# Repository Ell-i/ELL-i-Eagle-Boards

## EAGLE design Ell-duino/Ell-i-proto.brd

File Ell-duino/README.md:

Ell-duino -- the first ELL-i prototype board
============================================

This directory contains the Ell-duino Ell-i board design, mainly for
historical reasons.

Ell-duino was the very first PCB produced by the Ell-i co-operative,
with 50 pieces manufactured in late May 2013.  It was an
STM32F051-based board, header-compatible with Arduino.  It taught us a
lot, guiding us with designing the next round of boards, and acting as
a testing platform even after that.

Used libraries
--------------

Contrary to the other projects in this repository, this design used a
local Eagle library, ell-i.lbr.  By now that library is obsolete and
should not be used any more.  Instead, you are adviced to use the
components from the SparkFun or ELL-i Eagle libraries.

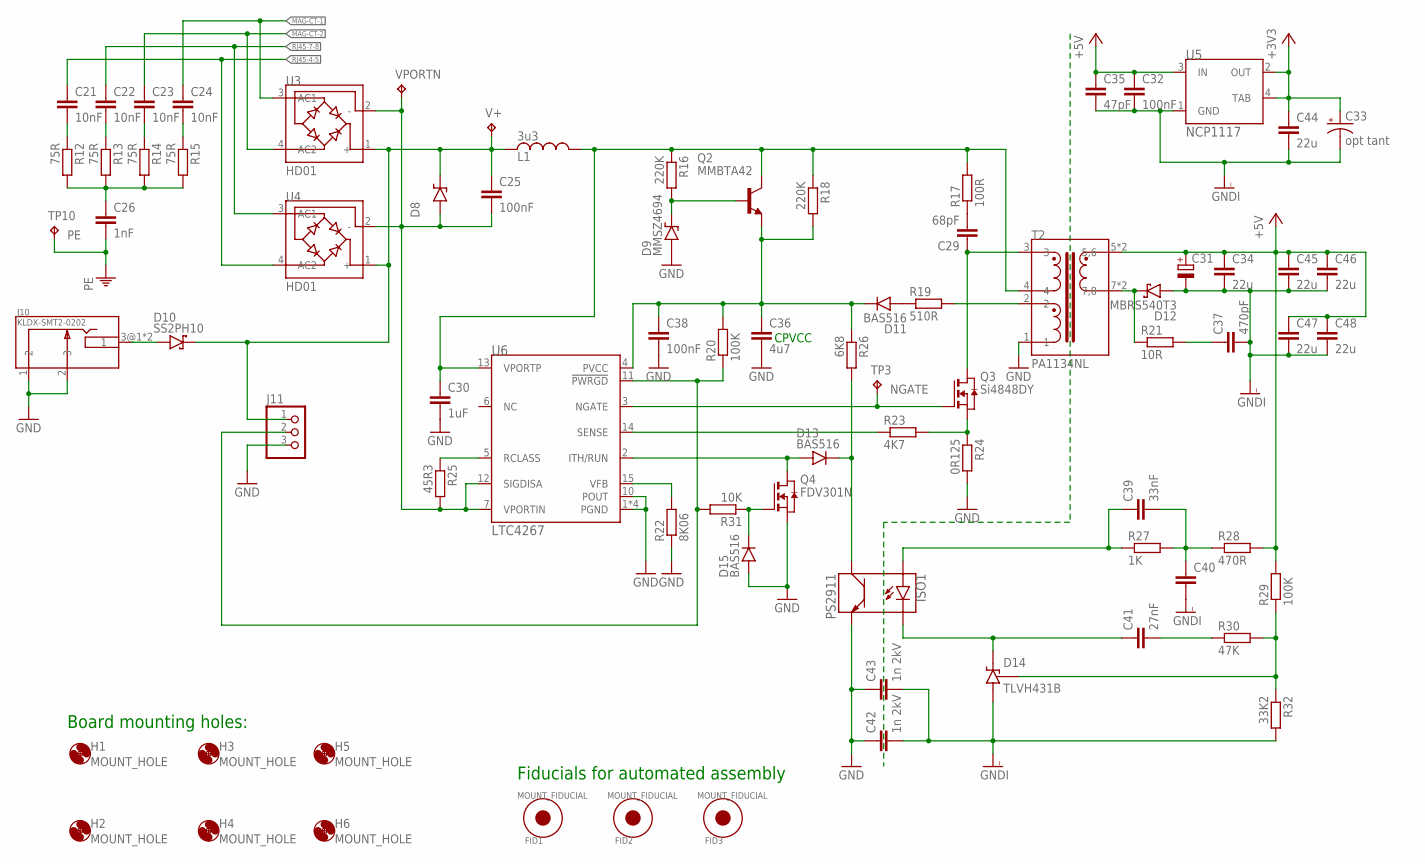
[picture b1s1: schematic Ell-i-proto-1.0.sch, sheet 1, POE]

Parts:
C21, C22, C23, C24: 10nF; 0603
C25: 100nF; 0805
C26: 1nF; C1206
C29: 68pF; 0805
C30: 1uF; 0805
C31: CPOL-EU153CLV-0605; 153CLV-0605
C32, C38: 100nF; 0402
C33: opt tant; CT3216
C34, C44, C45, C46, C47, C48: 22u; 0805
C35: 47pF; 0402
C36: 4u7; 0805
C37: 470pF; 0402
C39: 33nF; 0402
C40: C0402; 0402
C41: 27nF; 0402
C42, C43: 1n 2kV; C1206
D8: SMAJ58A; SMA
D9: MMSZ4694; SOD-123
D10: SS2PH10; SMP
D11, D13, D15: BAS516; SOD523
D12: MBRS540T3; SMC
D14: TLVH431B; SOT23
FID1, FID2, FID3: MOUNT_FIDUCIAL
H1, H2, H3, H4, H5, H6: MOUNT_HOLE
ISO1: PS2911
J10: KLDX-SMT2-0202
J11: PINHD-1X3; 1X03
L1: 3u3; MSS5121
Q2: MMBTA42; SOT23
Q3: Si4848DY; SO8
Q4: FDV301N; SOT23
R12, R13, R14, R15: 75R; 0603
R16, R18: 220K; 0402
R17: 100R; 0805
R19: 510R; 0402
R20, R29: 100K; 0402
R21: 10R; 0402
R22: 8K06; 0402
R23: 4K7; 0402
R24: 0R125; R1206
R25: 45R3; 0402
R26: 6K8; 0402
R27: 1K; 0402
R28: 470R; 0402
R30: 47K; 0402
R31: 10K; 0402
R32: 33K2; 0402
T2: PA1134NL
TP3, TP10: TPB1,27; B1,27
U3, U4: HD01; MINIDIP4
U5: NCP1117; SOT223
U6: LTC4267; SSOP16
V+: TPB1,27; B1,27
VPORTN: TPB1,27; B1,27

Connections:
+3V3: C33.+, C44.1, U5.2 (OUT), U5.4 (TAB); also elsewhere on the board
+5V: C31.+, C32.1, C34.1, C35.1, C45.1, C46.1, C47.1, C48.1, R28.2, R29.2, T2.5 (5,6), T2.6 (5,6), U5.3 (IN); also elsewhere on the board
GND: C30.2, C36.2, C38.2, C42.1, C43.1, D9.A, D15.2 (A), ISO1.3, J10.1 (2), J10.2 (3), J11.3, Q4.2 (S), R22.1, R24.2, T2.1, U6.1 (PGND), U6.8 (PGND), U6.9 (PGND), U6.10 (POUT), U6.16 (PGND)
GNDI: C31.-, C32.2, C33.-, C34.2, C35.2, C37.2, C40.2, C42.2, C43.2, C44.2, C45.2, C46.2, C47.2, C48.2, D12.2 (A), D14.3 (A), R32.2, U5.1 (GND); also elsewhere on the board
MAG-CT-1: C24.1, U3.3 (AC1); also elsewhere on the board
MAG-CT-2: C23.1, U3.4 (AC2); also elsewhere on the board
N22741: C21.2, R12.1
N22792: C22.2, R13.1
N22914: C26.1, R12.2, R13.2, R14.2, R15.2
N23144: C23.2, R14.1
N23171: C24.2, R15.1
N27571: C29.1, Q3.P$5 (D), Q3.P$6 (D), Q3.P$7 (D), Q3.P$8 (D), T2.3
N27735: Q3.P$1 (S), Q3.P$2 (S), Q3.P$3 (S), R23.2, R24.1
N28455: R23.1, U6.14 (SENSE)
N30165: C36.1, C38.1, D11.1 (C), Q2.2 (E), R18.2, R20.2, R26.1, U6.4 (PVCC)
N30229: D11.2 (A), R19.1
N30416: D13.2 (A), Q4.3 (D), U6.2 (ITH/RUN)
N32035: D15.1 (C), Q4.1 (G), R31.1
N36998: R22.2, U6.15 (VFB)
N40108: D14.1 (REF), R29.1, R30.2, R32.1
N40137: C41.1, D14.2 (C), ISO1.2
N40177: C39.1, ISO1.1, R27.1
N40361: D12.1 (C), R21.1, T2.7 (7,8), T2.8 (7,8)
N40778: C37.1, R21.2
N62909: C30.1, L1.2, Q2.3 (C), R16.1, R17.2, R18.1, T2.4, U6.13 (VPORTP)
N62998: D9.C, Q2.1 (B), R16.2
N64947: R25.1, U6.5 (RCLASS)
N68062: R19.2, T2.2
N68837: C29.2, R17.1
N69576: D13.1 (C), ISO1.4, R26.2
N69902: C41.2, R30.1
N70322: C39.2, C40.1, R27.2, R28.1
N184903: D10.A, J10.3@1 (1), J10.3@2 (1)
NGATE: Q3.P$4 (G), TP3.TP, U6.3 (NGATE)
NPWRGD: J11.2, R20.1, R31.2, U6.11 (!PWRGD)
PE: C26.2, TP10.TP; also elsewhere on the board
RJ45-4-5: C21.1, U4.4 (AC2); also elsewhere on the board
RJ45-7-8: C22.1, U4.3 (AC1); also elsewhere on the board
V+: C25.1, D8.1 (C), D10.C, J11.1, L1.1, U3.1 (+), U4.1 (+), V+.TP
VPORTN: C25.2, D8.2 (A), R25.2, U3.2 (-), U4.2 (-), U6.7 (VPORTIN), U6.12 (SIGDISA), VPORTN.TP

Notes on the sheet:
CPVCC
Board mounting holes:
Fiducials for automated assembly

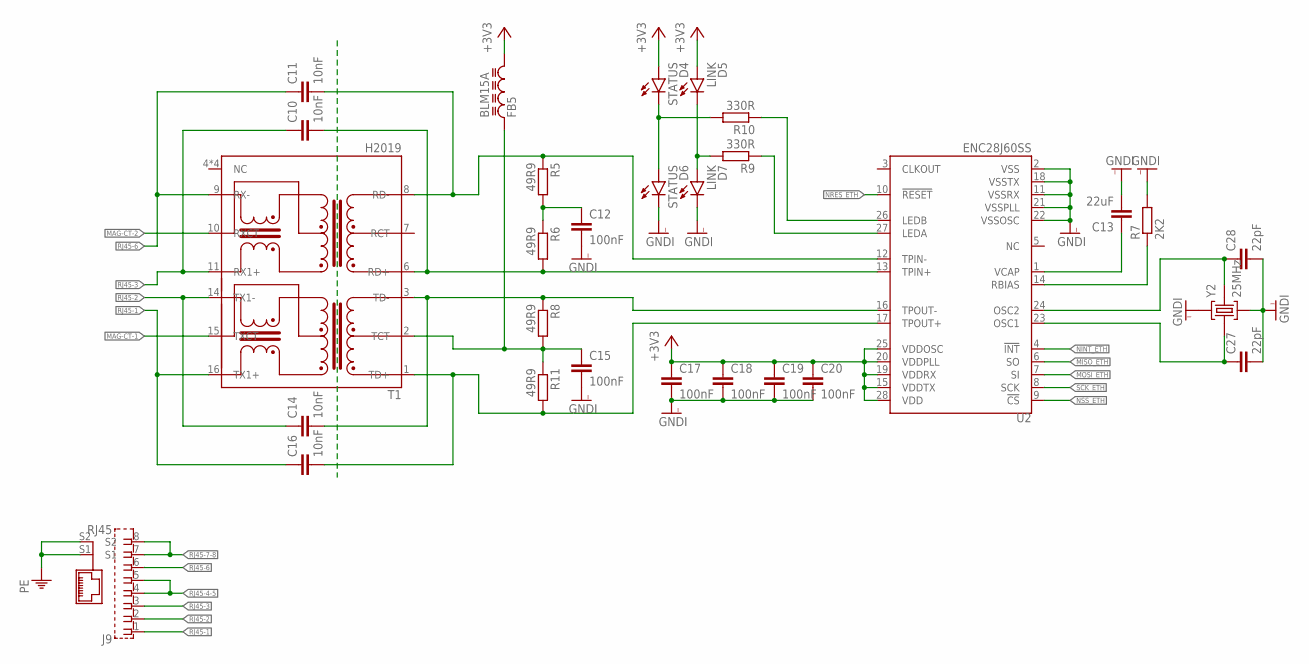
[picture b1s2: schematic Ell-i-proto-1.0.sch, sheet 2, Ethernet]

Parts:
C10, C11, C14, C16: 10nF; C1206
C12, C15, C17, C18, C19, C20: 100nF; 0402
C13: 22uF; 0805
C27, C28: 22pF; 0402
D4, D6: STATUS; DIODE0603
D5, D7: LINK; DIODE0603
FB5: BLM15A; 0402
J9: RJ45; 85502-5008
R5, R6, R8, R11: 49R9; 0402
R7: 2K2; 0402
R9, R10: 330R; 0402
T1: H2019; H2019NL
U2: ENC28J60SS; SSOP28DB
Y2: 25MHz; XTAL3225

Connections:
+3V3: C17.1, C18.1, C19.1, C20.1, D4.2 (A), D5.2 (A), FB5.2, U2.15 (VDDTX), U2.19 (VDDRX), U2.20 (VDDPLL), U2.25 (VDDOSC), U2.28 (VDD); also elsewhere on the board
GNDI: C12.2, C13.2, C15.2, C17.2, C18.2, C19.2, C20.2, C27.2, C28.2, D6.1 (C), D7.1 (C), R7.2, U2.2 (VSS), U2.11 (VSSRX), U2.18 (VSSTX), U2.21 (VSSPLL), U2.22 (VSSOSC), Y2.2 (GND), Y2.4 (GND); also elsewhere on the board
MAG-CT-1: T1.15 (TXCT); also elsewhere on the board
MAG-CT-2: T1.10 (RXCT); also elsewhere on the board
MISO_ETH: U2.6 (SO); also elsewhere on the board
MOSI_ETH: U2.7 (SI); also elsewhere on the board
N08557: C14.2, R8.1, T1.3 (TD-), U2.16 (TPOUT-)
N08738: C16.2, R11.2, T1.1 (TD+), U2.17 (TPOUT+)
N08782: C10.2, R6.2, T1.6 (RD+), U2.13 (TPIN+)
N08928: C11.2, R5.1, T1.8 (RD-), U2.12 (TPIN-)
N12266: C15.1, FB5.1, R8.2, R11.1, T1.2 (TCT)
N12583: R7.1, U2.14 (RBIAS)
N13468: C28.1, U2.24 (OSC2), Y2.3 (C2)
N13660: C27.1, U2.23 (OSC1), Y2.1 (C1)
N14101: C13.1, U2.1 (VCAP)
N16078: C12.1, R5.2, R6.1
N181699: R9.1, U2.27 (LEDA)
N181770: R10.1, U2.26 (LEDB)
N182309: D4.1 (C), D6.2 (A), R10.2
unnamed: D5.1 (C), D7.2 (A), R9.2
NINT_ETH: U2.4 (!INT); also elsewhere on the board
NRES_ETH: U2.10 (!RESET); also elsewhere on the board
NSS_ETH: U2.9 (!CS); also elsewhere on the board
PE: J9.S1, J9.S2; also elsewhere on the board
RJ45-1: C16.1, J9.1, T1.16 (TX1+)
RJ45-2: C14.1, J9.2, T1.14 (TX1-)
RJ45-3: C10.1, J9.3, T1.11 (RX1+)
RJ45-4-5: J9.4, J9.5; also elsewhere on the board
RJ45-6: C11.1, J9.6, T1.9 (RX-)
RJ45-7-8: J9.7, J9.8; also elsewhere on the board
SCK_ETH: U2.8 (SCK); also elsewhere on the board

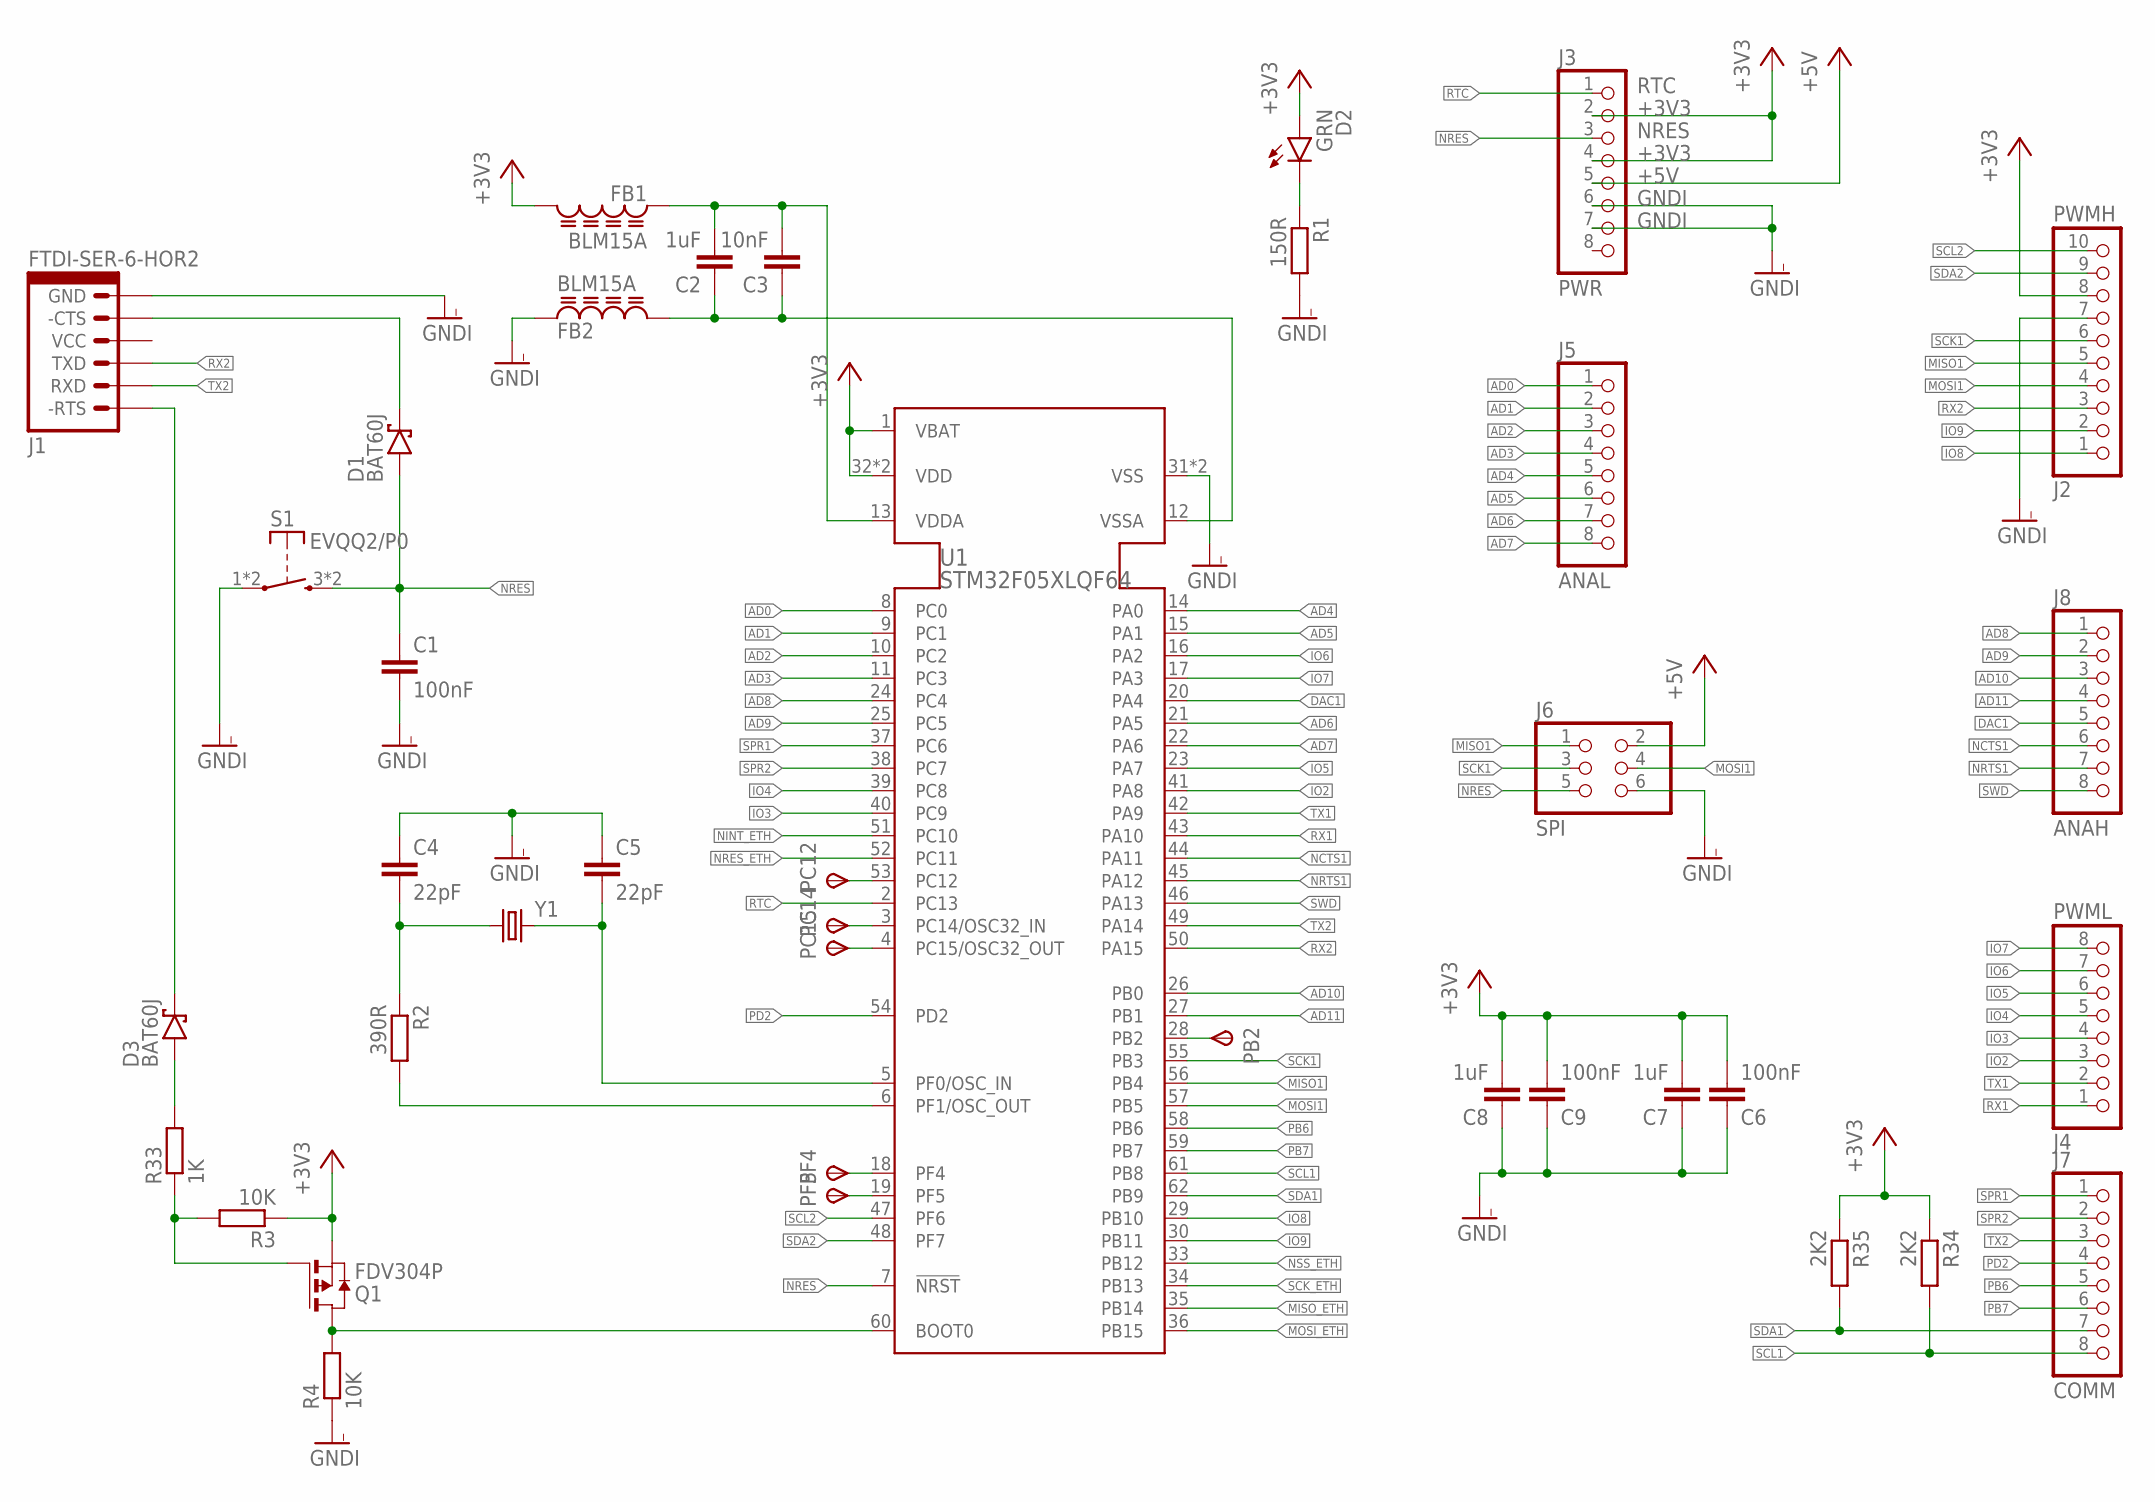
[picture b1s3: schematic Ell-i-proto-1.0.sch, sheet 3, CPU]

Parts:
C1, C6, C9: 100nF; 0402
C2, C7, C8: 1uF; 0402
C3: 10nF; 0402
C4, C5: 22pF; 0402
D1, D3: BAT60J; SOD323_DIODE
D2: GRN; DIODE0603
FB1, FB2: BLM15A; 0402
J1: FTDI-SER-6-HOR2; TSM-106-01-L-SH-REV
J2: PWMH; 1X10
J3: PWR; 1X08
J4: PWML; 1X08
J5: ANAL; 1X08
J6: SPI; 2X03
J7: COMM; 1X08
J8: ANAH; 1X08
PB2: TPSB1,27; B1,27
PC12, PC14, PC15: TPSB1,27; B1,27
PF4, PF5: TPSB1,27; B1,27
Q1: FDV304P; SOT23
R1: 150R; 0402
R2: 390R; 0402
R3, R4: 10K; 0402
R33: 1K; 0402
R34, R35: 2K2; 0402
S1: EVQQ2/P0
U1: STM32F05XLQF64; LQFP64
Y1: CRYSTALSM49; SM49

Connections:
+3V3: C6.2, C7.2, C8.2, C9.2, D2.2 (A), FB1.2, J2.8, J3.2, J3.4, Q1.2 (S), R3.1, R34.1, R35.1, U1.1 (VBAT), U1.32 (VDD), U1.64 (VDD); also elsewhere on the board
+5V: J3.5, J6.2; also elsewhere on the board
AD0: J5.1, U1.8 (PC0)
AD1: J5.2, U1.9 (PC1)
AD2: J5.3, U1.10 (PC2)
AD3: J5.4, U1.11 (PC3)
AD4: J5.5, U1.14 (PA0)
AD5: J5.6, U1.15 (PA1)
AD6: J5.7, U1.21 (PA5)
AD7: J5.8, U1.22 (PA6)
AD8: J8.1, U1.24 (PC4)
AD9: J8.2, U1.25 (PC5)
AD10: J8.3, U1.26 (PB0)
AD11: J8.4, U1.27 (PB1)
DAC1: J8.5, U1.20 (PA4)
GNDI: C1.2, C4.1, C5.1, C6.1, C7.1, C8.1, C9.1, FB2.1, J1.1 (GND), J2.7, J3.6, J3.7, J6.6, R1.2, R4.1, S1.1, S1.2, U1.31 (VSS), U1.63 (VSS); also elsewhere on the board
IO2: J4.3, U1.41 (PA8)
IO3: J4.4, U1.40 (PC9)
IO4: J4.5, U1.39 (PC8)
IO5: J4.6, U1.23 (PA7)
IO6: J4.7, U1.16 (PA2)
IO7: J4.8, U1.17 (PA3)
IO8: J2.1, U1.29 (PB10)
IO9: J2.2, U1.30 (PB11)
MISO1: J2.5, J6.1, U1.56 (PB4)
MISO_ETH: U1.35 (PB14); also elsewhere on the board
MOSI1: J2.4, J6.4, U1.57 (PB5)
MOSI_ETH: U1.36 (PB15); also elsewhere on the board
N41567: D2.1 (C), R1.1
N98218: C2.1, C3.1, FB2.2, U1.12 (VSSA)
N100630: C2.2, C3.2, FB1.1, U1.13 (VDDA)
N118561: Q1.3 (D), R4.2, U1.60 (BOOT0)
N205481: C4.2, R2.1, Y1.1
N209164: Q1.1 (G), R3.2, R33.1
N230488: D3.2 (A), R33.2
unnamed: PC14.TP, U1.3 (PC14/OSC32_IN)
unnamed: PC15.TP, U1.4 (PC15/OSC32_OUT)
unnamed: PF4.TP, U1.18 (PF4)
unnamed: D1.1 (C), J1.2 (-CTS)
unnamed: PF5.TP, U1.19 (PF5)
unnamed: PB2.TP, U1.28 (PB2)
unnamed: PC12.TP, U1.53 (PC12)
NCTS1: J8.6, U1.44 (PA11)
NDSR2: D3.1 (C), J1.6 (-RTS)
NINT_ETH: U1.51 (PC10); also elsewhere on the board
NRES: C1.1, D1.2 (A), J3.3, J6.5, S1.3 (S), S1.4 (S), U1.7 (!NRST)
NRES_ETH: U1.52 (PC11); also elsewhere on the board
NRTS1: J8.7, U1.45 (PA12)
NSS_ETH: U1.33 (PB12); also elsewhere on the board
PB6: J7.5, U1.58 (PB6)
PB7: J7.6, U1.59 (PB7)
PD2: J7.4, U1.54 (PD2)
PF0: C5.2, U1.5 (PF0/OSC_IN), Y1.2
PF1: R2.2, U1.6 (PF1/OSC_OUT)
RTC: J3.1, U1.2 (PC13)
RX1: J4.1, U1.43 (PA10)
RX2: J1.4 (TXD), J2.3, U1.50 (PA15)
SCK1: J2.6, J6.3, U1.55 (PB3)
SCK_ETH: U1.34 (PB13); also elsewhere on the board
SCL1: J7.8, R34.2, U1.61 (PB8)
SCL2: J2.10, U1.47 (PF6)
SDA1: J7.7, R35.2, U1.62 (PB9)
SDA2: J2.9, U1.48 (PF7)
SPR1: J7.1, U1.37 (PC6)
SPR2: J7.2, U1.38 (PC7)
SWD: J8.8, U1.46 (PA13)
TX1: J4.2, U1.42 (PA9)
TX2: J1.5 (RXD), J7.3, U1.49 (PA14)

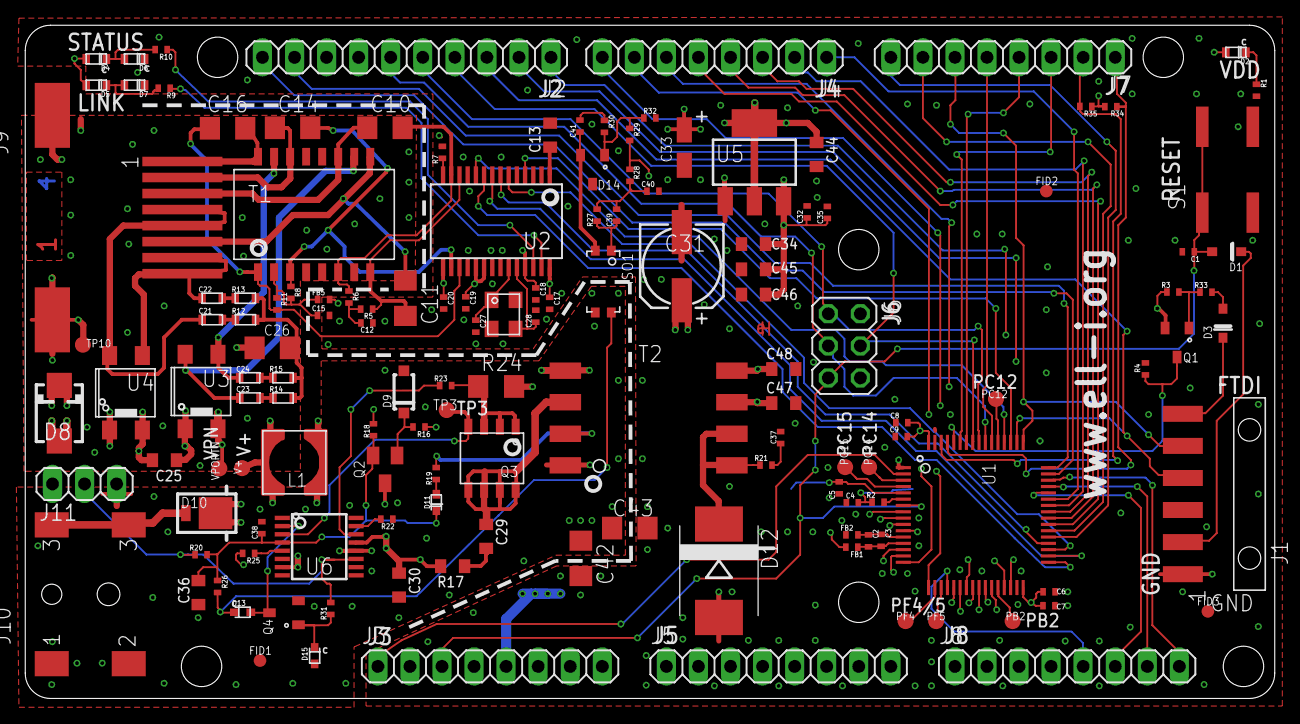
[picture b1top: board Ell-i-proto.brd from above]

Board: 4 copper layers, 99.0 x 53.3 mm, 149 parts (1 on the bottom side), 123 nets.

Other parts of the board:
U$4: EH-LOGO

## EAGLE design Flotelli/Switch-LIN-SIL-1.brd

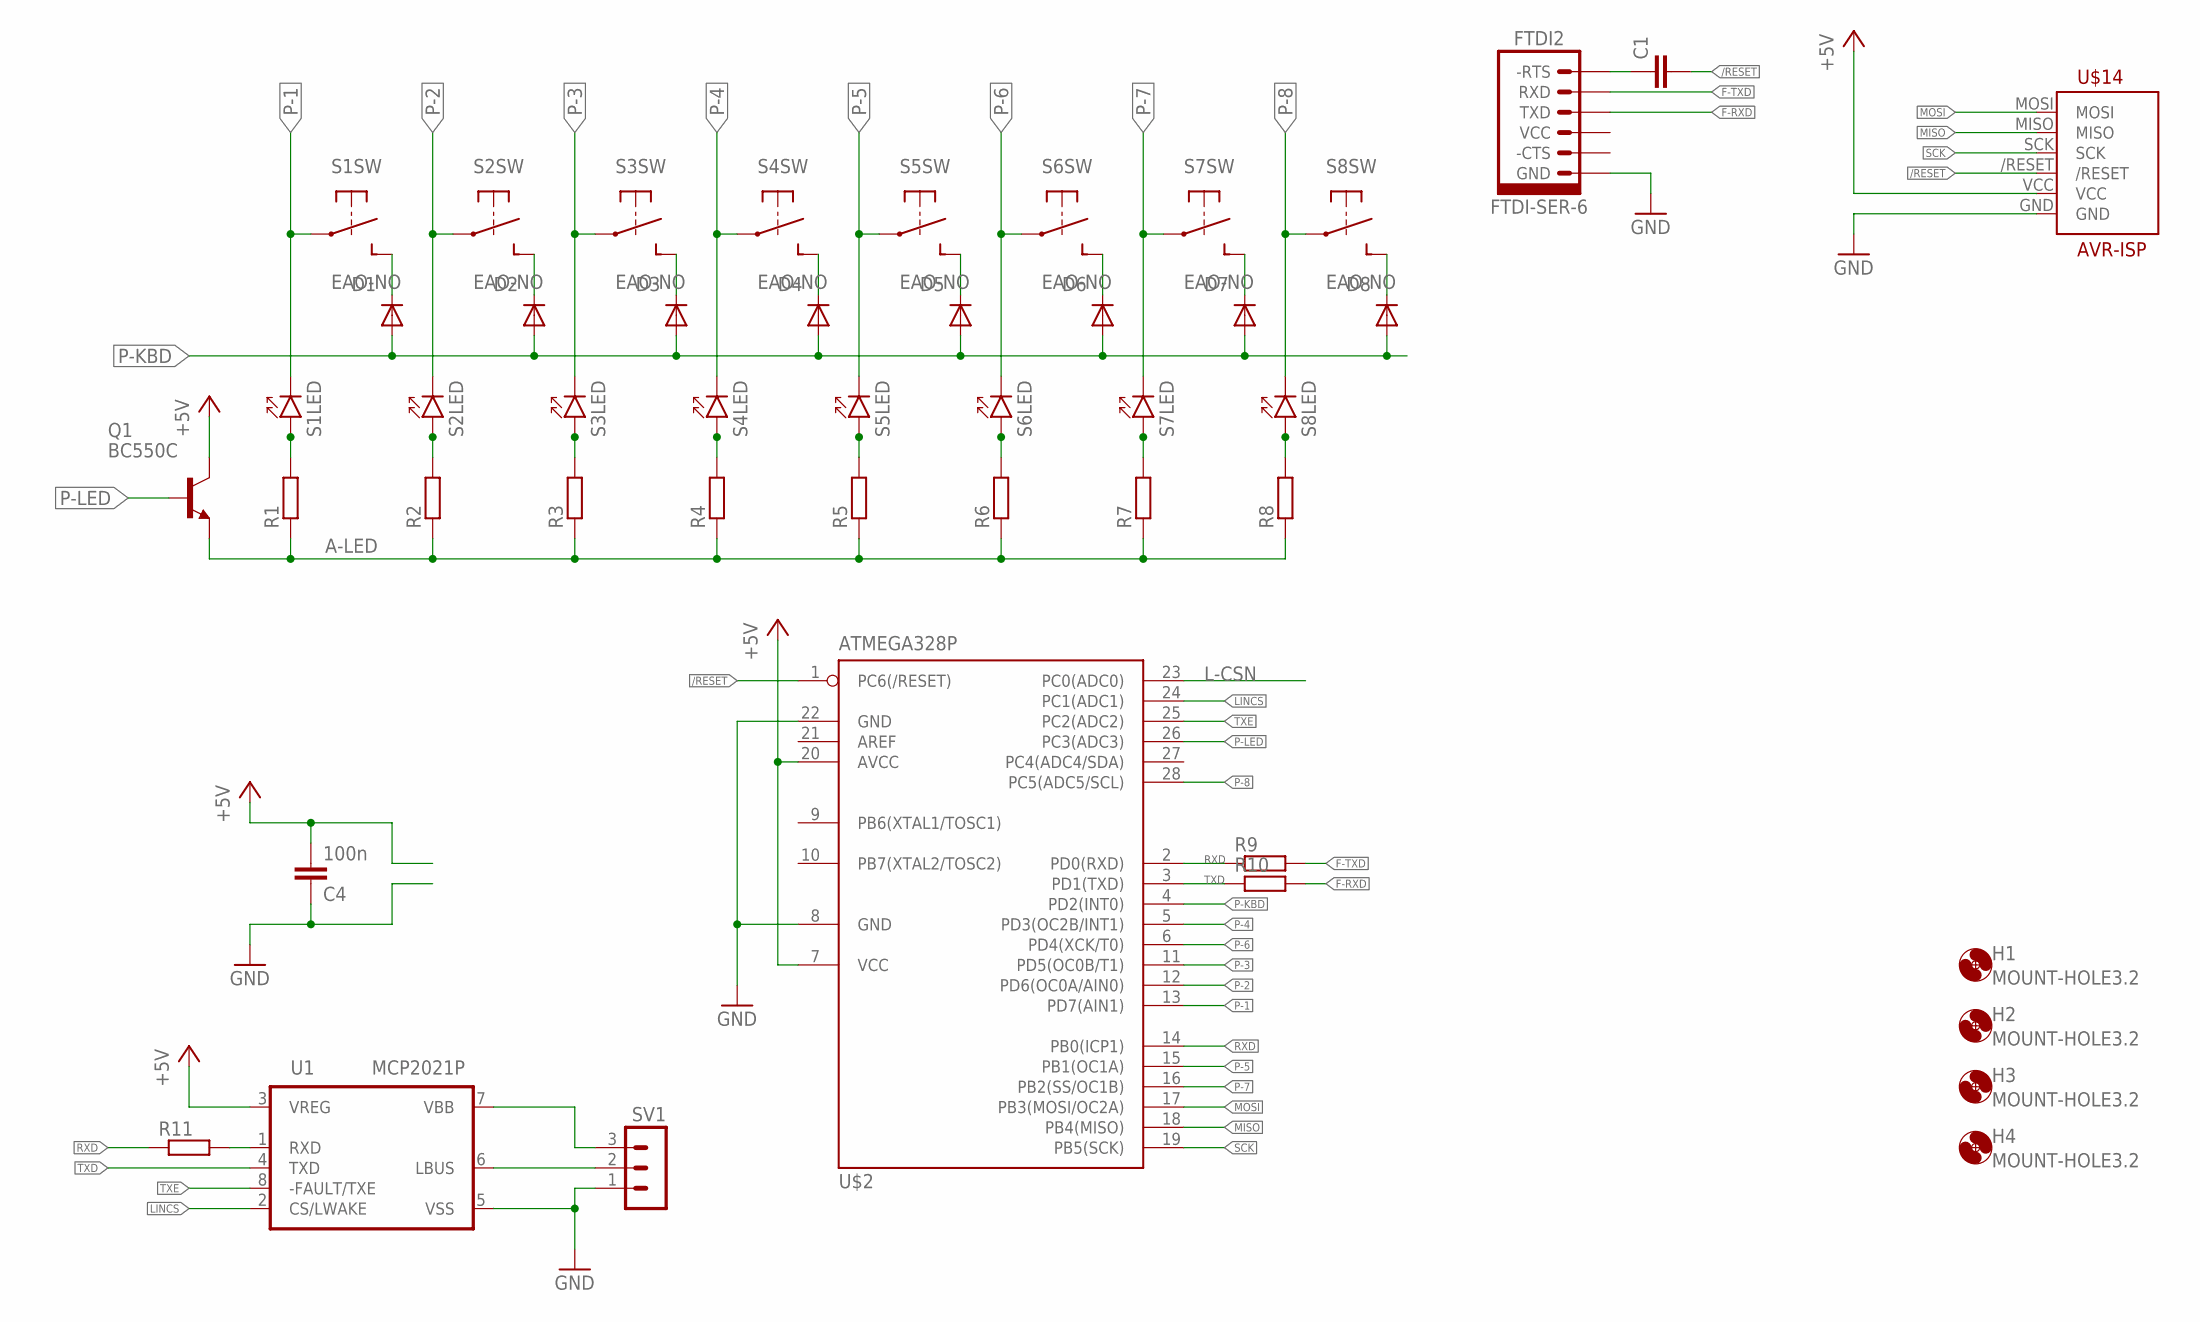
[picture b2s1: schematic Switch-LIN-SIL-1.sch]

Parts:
C1: C-EU025-025X050; C025-025X050
C4: 100n; C0805
D1, D2, D3, D4, D5, D6, D7, D8: 1N4148; DO35-7
FTDI2: FTDI-SER-6
H1, H2, H3, H4: MOUNT-HOLE3.2; 3,2
Q1: BC550C; TO92-EBC
R1, R2, R3, R4, R5, R6, R7, R8, R9, R10, R11: R-EU_0207/7; 0207/7
S1, S2, S3, S4, S5, S6, S7, S8: EAO-NO; MA04-1
SV1: MA03-1
U1: MCP2021P; DIL8
U$2: ATMEGA328P; DIL28-3
U$14: AVR-ISP; AVR-ISP-SIL

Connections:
+5V: C4.2, Q1.C, U1.3 (VREG), U$2.7 (VCC), U$2.20 (AVCC), U$14.VCC
/RESET: C1.2, U$2.1 (PC6(/RESET)), U$14./RESET
A-LED: Q1.E, R1.1, R2.1, R3.1, R4.1, R5.1, R6.1, R7.1, R8.1
F-RTS: C1.1, FTDI2.-RTS
F-RXD: FTDI2.TXD, R10.2
F-TXD: FTDI2.RXD, R9.2
GND: C4.1, FTDI2.GND, SV1.1, U1.5 (VSS), U$2.8 (GND), U$2.22 (GND), U$14.GND
L-CSN: U$2.23 (PC0(ADC0))
L-RXD: R11.2, U1.1 (RXD)
LBUS: SV1.2, U1.6 (LBUS)
LINCS: U1.2 (CS/LWAKE), U$2.24 (PC1(ADC1))
MISO: U$2.18 (PB4(MISO)), U$14.MISO
MOSI: U$2.17 (PB3(MOSI/OC2A)), U$14.MOSI
unnamed: D1.C, S1.4 (NO2)
unnamed: D2.C, S2.4 (NO2)
unnamed: D3.C, S3.4 (NO2)
unnamed: D4.C, S4.4 (NO2)
unnamed: D5.C, S5.4 (NO2)
unnamed: D6.C, S6.4 (NO2)
unnamed: D7.C, S7.4 (NO2)
unnamed: D8.C, S8.4 (NO2)
unnamed: R1.2, S1.2 (A)
unnamed: R2.2, S2.2 (A)
unnamed: R3.2, S3.2 (A)
unnamed: R4.2, S4.2 (A)
unnamed: R5.2, S5.2 (A)
unnamed: R6.2, S6.2 (A)
unnamed: R7.2, S7.2 (A)
unnamed: R8.2, S8.2 (A)
P-1: S1.1 (C), S1.3 (NO1), U$2.13 (PD7(AIN1))
P-2: S2.1 (C), S2.3 (NO1), U$2.12 (PD6(OC0A/AIN0))
P-3: S3.1 (C), S3.3 (NO1), U$2.11 (PD5(OC0B/T1))
P-4: S4.1 (C), S4.3 (NO1), U$2.5 (PD3(OC2B/INT1))
P-5: S5.1 (C), S5.3 (NO1), U$2.15 (PB1(OC1A))
P-6: S6.1 (C), S6.3 (NO1), U$2.6 (PD4(XCK/T0))
P-7: S7.1 (C), S7.3 (NO1), U$2.16 (PB2(SS/OC1B))
P-8: S8.1 (C), S8.3 (NO1), U$2.28 (PC5(ADC5/SCL))
P-KBD: D1.A, D2.A, D3.A, D4.A, D5.A, D6.A, D7.A, D8.A, U$2.4 (PD2(INT0))
P-LED: Q1.B, U$2.26 (PC3(ADC3))
RXD: R9.1, R11.1, U$2.2 (PD0(RXD)), U$2.14 (PB0(ICP1))
SCK: U$2.19 (PB5(SCK)), U$14.SCK
TXD: R10.1, U1.4 (TXD), U$2.3 (PD1(TXD))
TXE: U1.8 (-FAULT/TXE), U$2.25 (PC2(ADC2))
VBB: SV1.3, U1.7 (VBB)

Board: 2 copper layers, 39 parts (1 on the bottom side), 43 nets, no tracks yet.

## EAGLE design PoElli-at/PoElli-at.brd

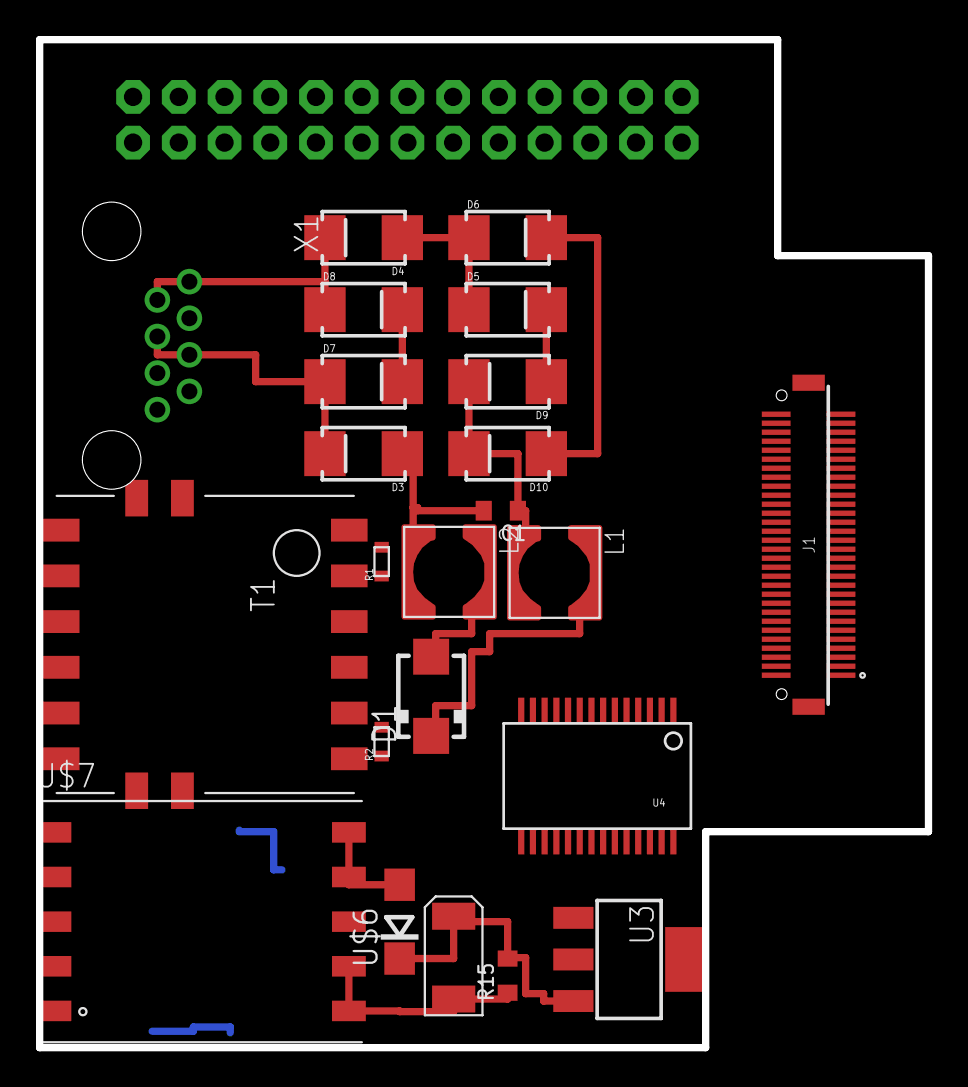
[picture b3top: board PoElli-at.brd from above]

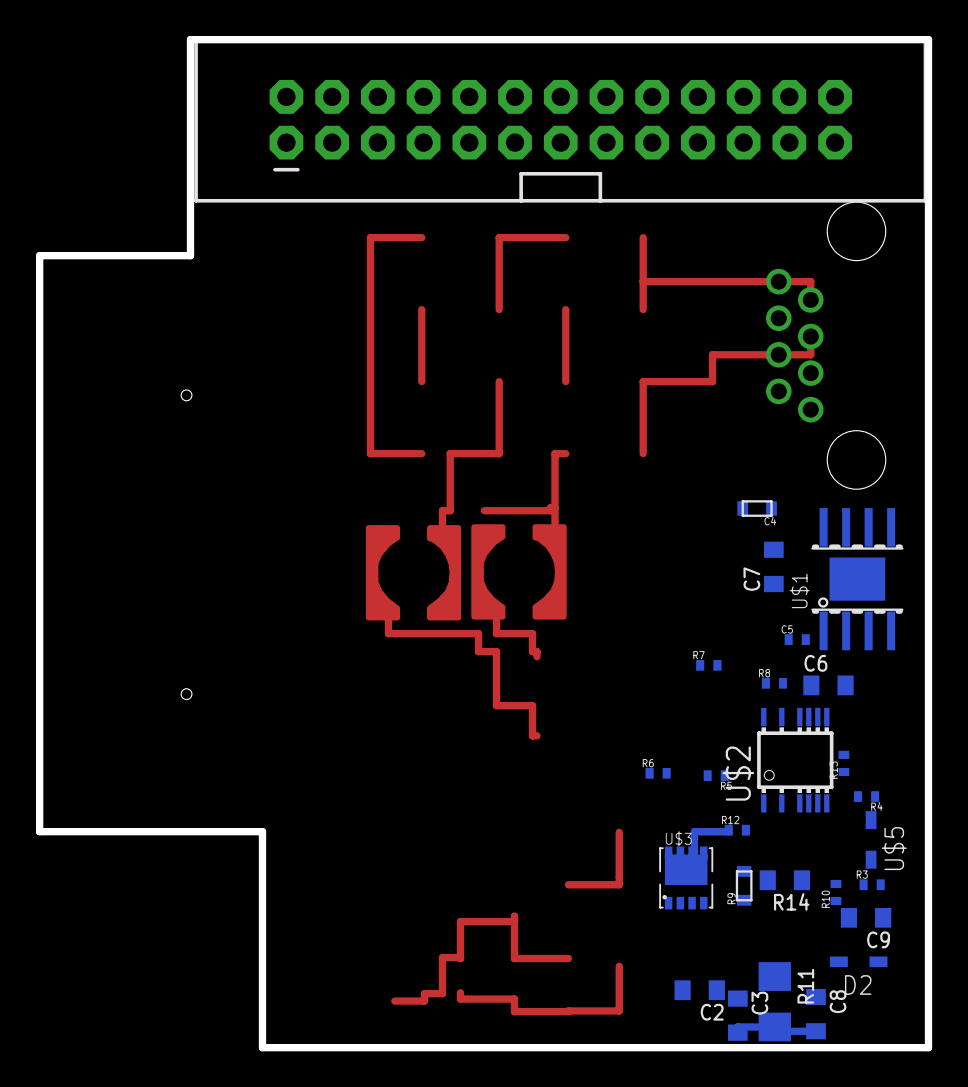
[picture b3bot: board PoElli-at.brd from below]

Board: 2 copper layers, 49.4 x 56.0 mm, 49 parts (26 on the bottom side), 40 nets.

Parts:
C1, C2, C3, C6, C7, C8, C9: C0805
C4: C0603
C5: C0402
C10: CT6032
D1: SMA
D2: BAS70J; SOD323
D3, D4, D5, D6, D7, D8, D9, D10: B2100; DIODE-B2100
J1: DF12-60DP; DF12(4.0)-60DP-0.5V
L1, L2: COILCRAFT-MSS5121
R1, R2, R9: 100; R0603
R3, R4, R5, R6, R7, R8, R10, R12, R13: 100; R0402
R11: 100; R1206
R14, R15: 100; R0805
SV1: RASPBERRYPI-GPIOPTH; 2X13-SHROUDED
T1: POE-ISOLATION; COILCRAFT-ETH1-230L
U3: NCP1117; SOT223
U4: SSOP28DB
U$1: TPS2378; SO08-POWERPAD
U$2: LT3748; MSOP16(12)
U$3: FDMC2674; MLP8L33
U$5: BAV20WS; SOD323
U$6: 10MQ100N; DO214AC
U$7: FLYBACK750311689; WE_EP13_SMD_10PIN
X1: RJ45MOLEX; MOLEX-43860-0001

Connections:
3.3V: SV1.1, SV1.17
5V: SV1.2, SV1.4
GND: C3.2, C4.2, C5.2, C6.2, C7.2, C8.2, R6.1, R7.1, R11.2, R13.1, SV1.6, SV1.9, SV1.14, SV1.20, SV1.25, U$1.5, U$1.8, U$2.8, U$2.9, U$7.1
unnamed: T1.P$10, X1.2
unnamed: T1.P$9, X1.1
unnamed: T1.P$13, X1.3
unnamed: T1.P$14, X1.6
unnamed: D4.C, D8.A, X1.7, X1.8
unnamed: C1.1, D7.C, D8.C, D9.C, D10.C, L1.1
unnamed: D3.C, D7.A, X1.4, X1.5
unnamed: C1.2, D3.A, D4.A, D5.A, D6.A, L2.1
unnamed: D5.C, D9.A, T1.P$12
unnamed: D6.C, D10.A, T1.P$11
unnamed: R1.2, T1.P$1
unnamed: R1.1, T1.P$2
unnamed: R2.2, T1.P$5
unnamed: R2.1, T1.P$6
unnamed: C2.2, D1.2, L2.2, R4.1, U$1.4, U$1.POWERPAD
unnamed: C2.1, C3.1, C7.1, C9.1, D1.1, L1.2, R3.2, R5.2, R14.2, U$1.1, U$2.1, U$7.3
unnamed: R5.1, R6.2, U$2.3
unnamed: R3.1, U$1.2
unnamed: R4.2, U$1.3
unnamed: C4.1, U$1.7, U$2.10
unnamed: R7.2, U$2.12
unnamed: C6.1, R8.2, U$2.11
unnamed: C5.1, R8.1
unnamed: R9.2, U$2.6
unnamed: R9.1, U$3.4
unnamed: R10.2, U$2.7
unnamed: R10.1, R11.1, U$3.1, U$3.2, U$3.3
unnamed: R12.1, U$3.5, U$3.6, U$3.7, U$3.8, U$3.F1, U$5.1, U$7.5
unnamed: D2.1, U$7.2
unnamed: C8.1, D2.2, U$2.5
unnamed: R12.2, U$2.16
unnamed: R13.2, U$2.14
unnamed: C9.2, R14.1, U$5.2
unnamed: U$6.A, U$7.6, U$7.7
unnamed: C10.P$1, R15.2, U3.3, U$6.C
unnamed: C10.P$2, R15.1, U$7.9, U$7.10
unnamed: U3.2, U3.4, U4.15, U4.19, U4.20, U4.25, U4.28

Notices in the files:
parts and their libraries:
ELL-i-Passives: Originally copied from SparkFun-Passives.lbr, under SparkFun Creative Commons license.
ELL-i-Passives: Eagle package Copyright (c) SparkFun under Creative Commons v3.0 Share Alike license.
